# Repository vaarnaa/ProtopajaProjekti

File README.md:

# Prototype project

The project consists of a prototype for a local air cleaner device with IoT features. The prototype was built in the summer 2017 at the Aalto University's Protocamp course in co-operation with Consair Oy. The primary purpose of the device is to reduce construction workers exposure to waste particles while mixing mortar.

## How it works

### Mechanics

The enclosure of the device was built of plywood with the help of a 3D model. The air flow enters through the air vent in the front panel, passes through the filters in the middle and the fan in the rear of the device and then exits through the roof outlet.

### Microcontroller

The operation of the device is controlled by the microcontroller. It reads the values measured by the pressure sensors and adjusts the fan speed based on the measurement results. The airflow passing through the device is kept constant regardless of the degree of clogging of the filters.

### PID Control

The fan speed is controlled by a specific piece of software in the microcontroller. The code-based PID controller adjusts the speed to the desired value based on the difference between the measured and the desired speed.

### Networking

While the device is in operation, the GSM module connects to the server and transmits information about the status of the device. The server stores the data in the database. The person in charge of the device is informed by email or text message if the filters are clogged.

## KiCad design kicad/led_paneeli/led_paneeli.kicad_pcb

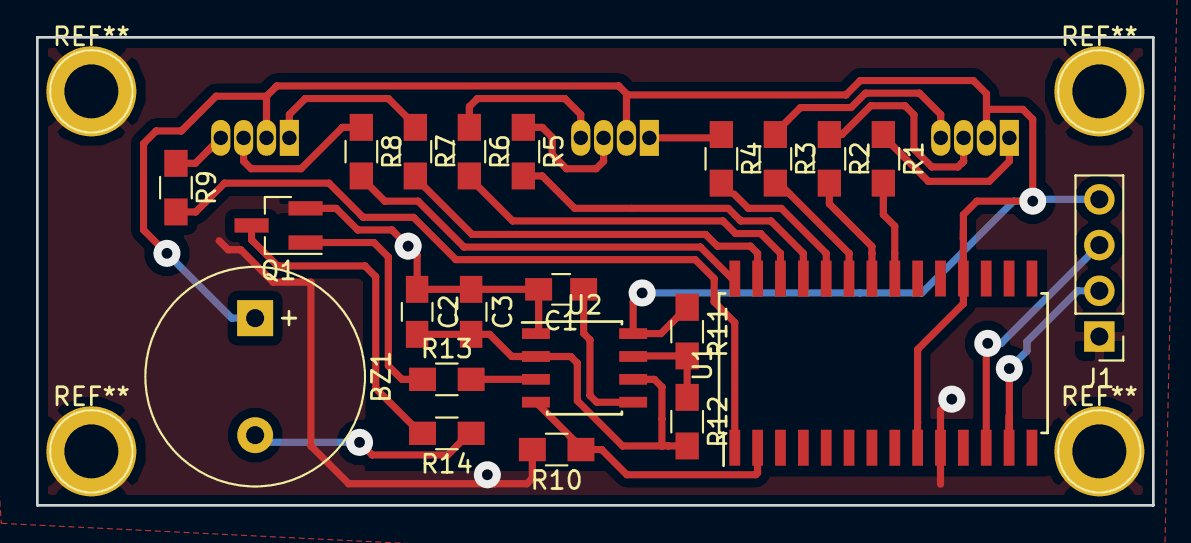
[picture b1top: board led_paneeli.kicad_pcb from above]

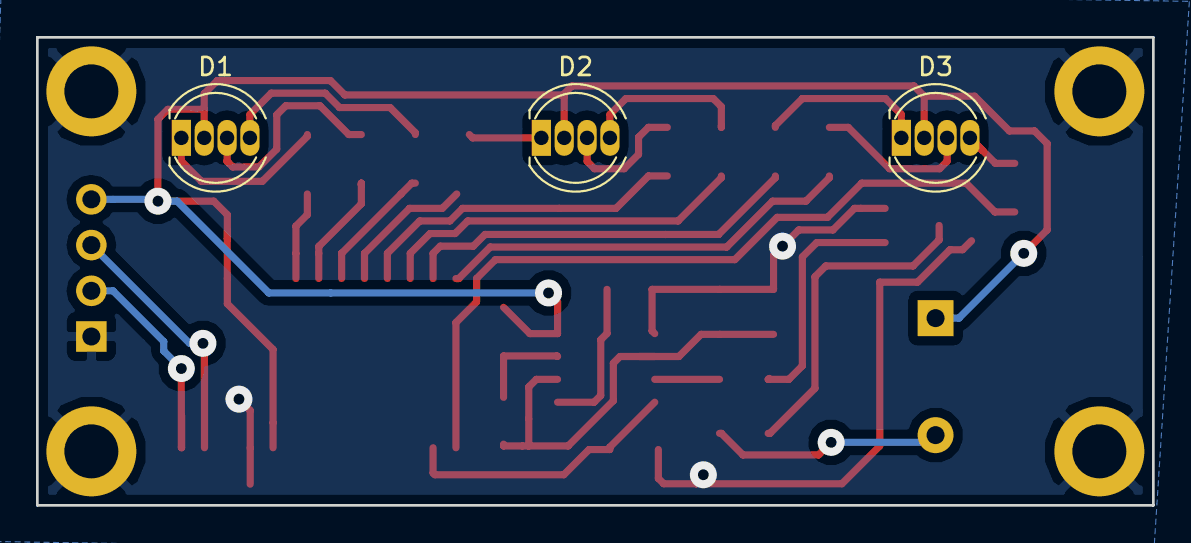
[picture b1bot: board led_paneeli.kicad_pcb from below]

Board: 2 copper layers, 62.0 x 26.0 mm, 25 parts (3 on the bottom side), 30 nets.

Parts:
BZ1: Buzzer; MagneticBuzzer_ProSignal_ABT-410-RC
C1: 10n; C_0805_HandSoldering
C2: 33n; C_0805_HandSoldering
C3: 22n; C_0805_HandSoldering
D1, D2, D3: LED_RAGB; LED_D5.0mm-4
J1: CONN_01X04; Pin_Header_Straight_1x04_Pitch2.54mm
Q1: PMV20XNE; SOT-23_Handsoldering
R1, R4, R7: 640; R_0805_HandSoldering
R2, R5, R8: 1k86; R_0805_HandSoldering
R3, R6, R9: 4k6; R_0805_HandSoldering
R10: 10k; R_0805_HandSoldering
R11: 1k; R_0805_HandSoldering
R12: 6k8; R_0805_HandSoldering
R13, R14: 330; R_0805_HandSoldering
U1: MCP23017; SOIC-28W_7.5x17.9mm_Pitch1.27mm
U2: NE555; SOIC-8_3.9x4.9mm_Pitch1.27mm

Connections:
+5V: BZ1.1, D1.2, D2.2, D3.2, J1.4, R11.1, U1.9, U1.18, U2.8
GND: C1.2, C2.1, C3.1, J1.1, Q1.2, R10.2, U1.10, U2.1
unnamed: BZ1.2, R14.1
unnamed: C1.1, U2.5
unnamed: C2.2, C3.2, R12.2, U2.2, U2.6
unnamed: D1.1, R1.1
unnamed: D1.3, R2.1
unnamed: D1.4, R3.1
unnamed: D2.1, R4.1
unnamed: D2.3, R5.1
unnamed: D2.4, R6.1
unnamed: D3.1, R7.1
unnamed: D3.3, R8.1
unnamed: D3.4, R9.1
unnamed: J1.2, U1.13
unnamed: J1.3, U1.12
unnamed: Q1.1, R13.1
unnamed: Q1.3, R14.2
unnamed: R1.2, U1.21
unnamed: R2.2, U1.22
unnamed: R3.2, U1.23
unnamed: R4.2, U1.24
unnamed: R5.2, U1.25
unnamed: R6.2, U1.26
unnamed: R7.2, U1.27
unnamed: R8.2, U1.28
unnamed: R9.2, U1.1
unnamed: R10.1, U1.2, U2.4
unnamed: R11.2, R12.1, U2.7
unnamed: R13.2, U2.3

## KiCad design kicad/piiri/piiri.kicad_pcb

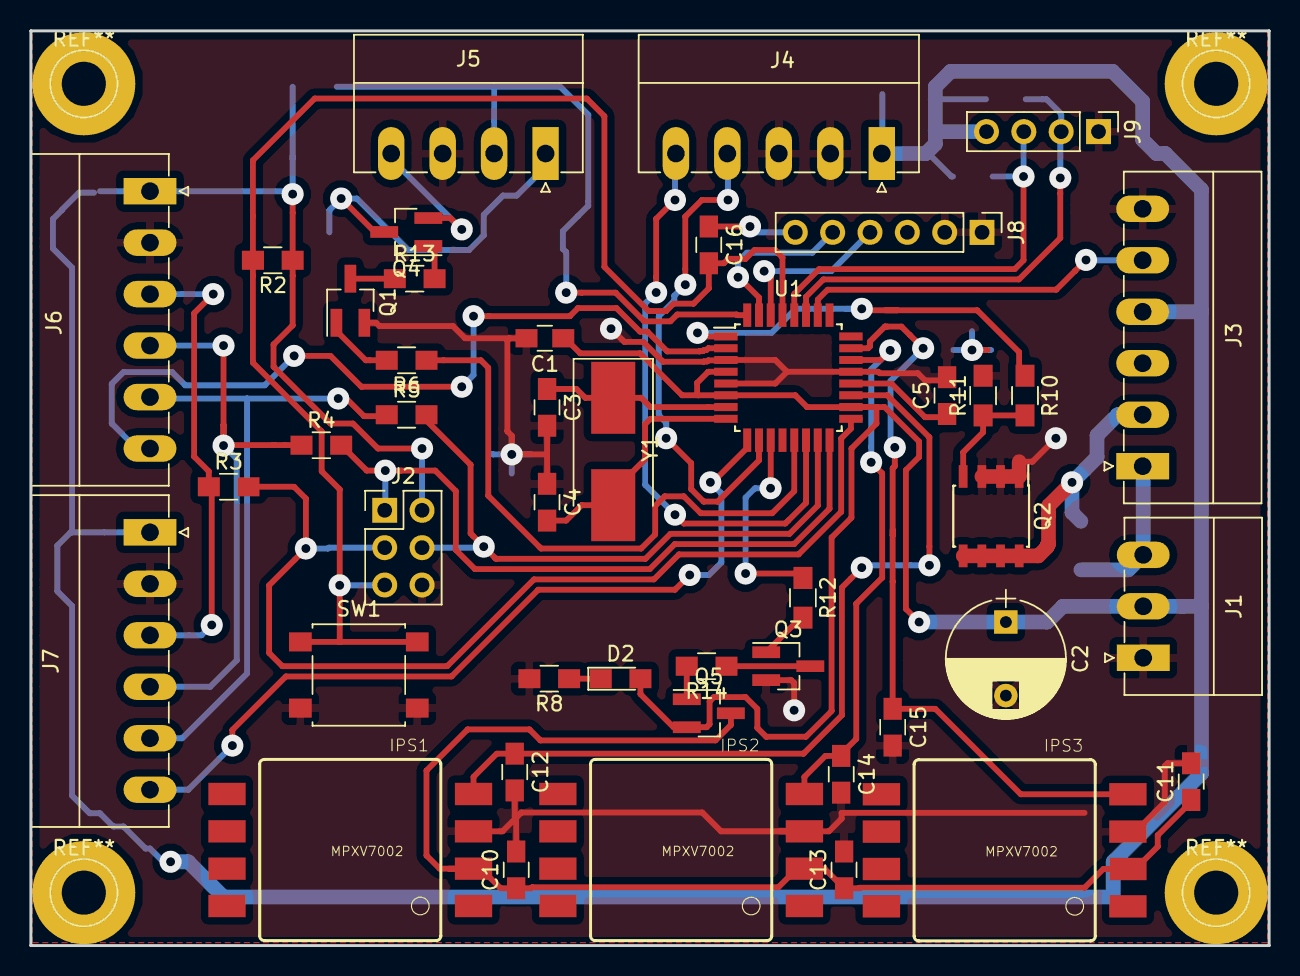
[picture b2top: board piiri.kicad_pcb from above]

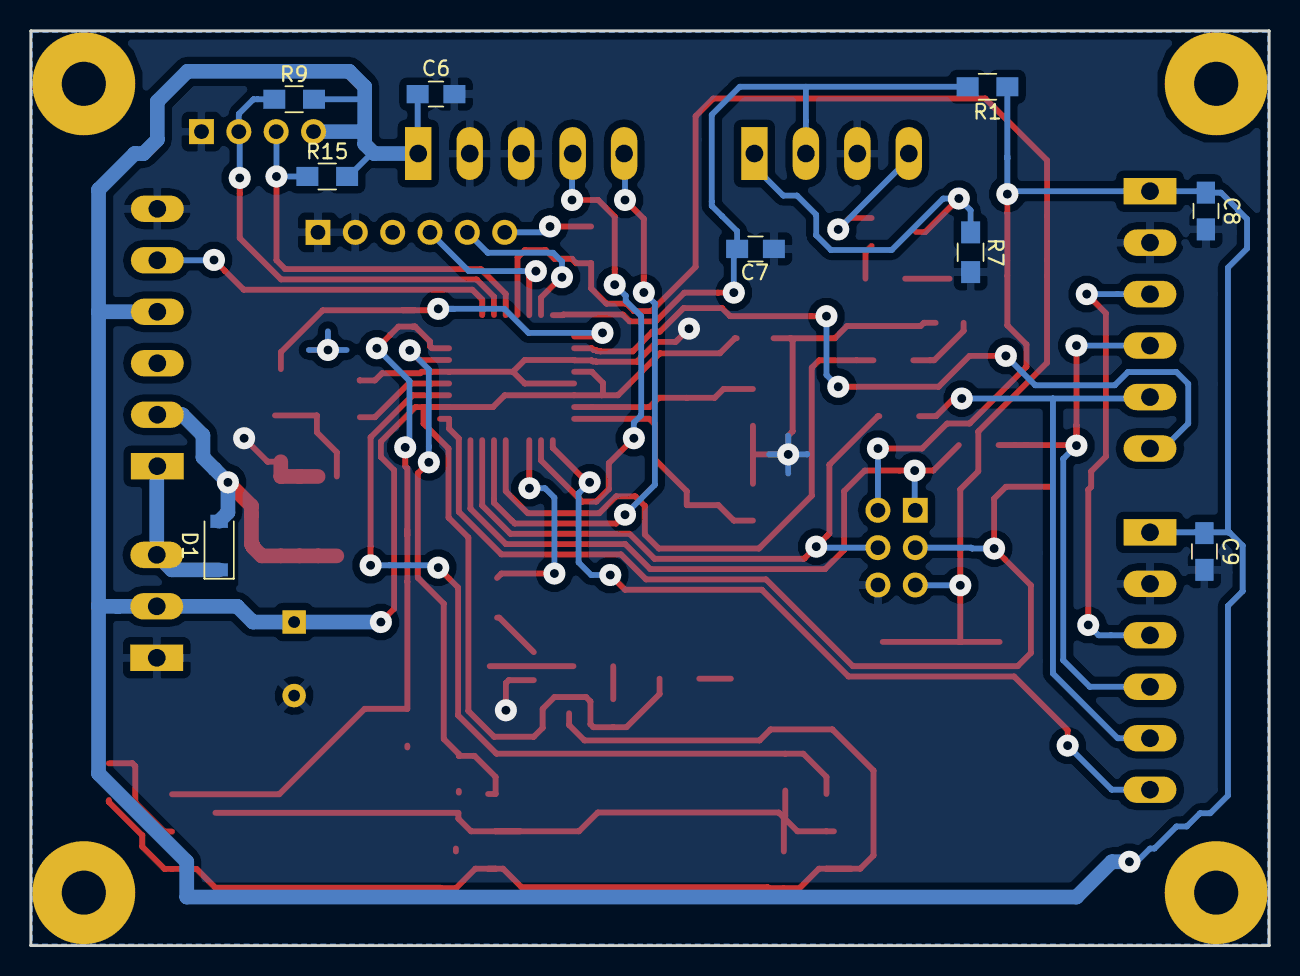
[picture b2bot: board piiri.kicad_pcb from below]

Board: 2 copper layers, 84.2 x 62.2 mm, 53 parts (9 on the bottom side), 42 nets.

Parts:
C1, C6, C7, C8, C9, C10, C11, C13, C16: 0.1uF; C_0805_HandSoldering
C2: 220uF; CP_Radial_D8.0mm_P5.00mm
C3, C4: 22pF; C_0805_HandSoldering
C5: 10nF; C_0805_HandSoldering
C12, C14, C15: 470pF; C_0805_HandSoldering
D1: D; D_SOD-123
D2: LED; LED_0805_HandSoldering
IPS1, IPS2, IPS3: MPXV7002; SOP8-1351
J1: VIRTA; PhoenixContact_MC-G_03x3.50mm_Angled
J2: ICSP; Pin_Header_Straight_2x03_Pitch2.54mm
J3: I/O; PhoenixContact_MC-G_06x3.50mm_Angled
J4: GSM; PhoenixContact_MC-G_05x3.50mm_Angled
J5: MOOTTORI; PhoenixContact_MC-G_04x3.50mm_Angled
J6: ANTURI1; PhoenixContact_MC-G_06x3.50mm_Angled
J7: ANTURI2; PhoenixContact_MC-G_06x3.50mm_Angled
J8: CONN_01X06; Pin_Header_Straight_1x06_Pitch2.54mm
J9: CONN_01X04; Pin_Header_Straight_1x04_Pitch2.54mm
Q1, Q3: BC818-40; SOT-23_Handsoldering
Q2: STS6NF20V; SOIC-8_3.9x4.9mm_Pitch1.27mm
Q4, Q5: BC578; SOT-23_Handsoldering
R1, R2, R6, R7, R11, R12, R13, R14: 10k; R_0805_HandSoldering
R3, R4, R5, R10: 560R; R_0805_HandSoldering
R8: 1k; R_0805_HandSoldering
R9, R15: 4k7; R_0805_HandSoldering
SW1: SW_Push; SW_SPST_B3S-1000
U1: ATMEGA328P-AU; TQFP-32_7x7mm_Pitch0.8mm
Y1: 16MHz; Crystal_SMD_7050-2pin_7.0x5.0mm_HandSoldering

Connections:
+5V: C1.1, C2.1, C6.1, C8.1, C9.1, D2.2, J1.2, J2.2, J3.4, J4.1, J6.1, J7.1, J9.4, Q5.2, R1.1, R2.1, R9.2, R15.2, U1.4, U1.6, U1.18
+12V: D1.1, J1.3, J3.1
GND: C1.2, C2.2, C3.2, C4.1, C5.2, C6.2, C7.2, C8.2, C9.2, C10.2, C11.2, C12.2, C13.2, C14.2, C15.2, IPS1.3, IPS2.3, IPS3.3, J1.1, J2.6, J3.6, J4.2, J4.3, J5.3, J6.2, J7.2, J8.1, J8.2, J9.1, Q1.2, Q2.1, Q2.2, Q2.3, Q3.2, R7.2, R8.2, R11.2, SW1.2, U1.3, U1.5, U1.21
IPS_A: C12.1, IPS1.4, U1.19
IPS_B: C14.1, IPS2.4, U1.22
IPS_C: C15.1, IPS3.4, U1.23
IPS_ON: R12.1, U1.11
IPS_PWR: C10.1, C11.1, C13.1, IPS1.2, IPS2.2, IPS3.2, Q5.3
MISO: J6.4, J7.4, R4.1
MOSI: J6.5, J7.5, R5.1
unnamed: C3.1, U1.7, Y1.1
unnamed: C4.2, U1.8, Y1.2
unnamed: C5.1, U1.20
unnamed: C16.1, J8.6
unnamed: D1.2, J3.2, Q2.5, Q2.6, Q2.7, Q2.8
unnamed: D2.1, R8.1
unnamed: J2.1, R4.2, U1.16
unnamed: J2.3, R3.2, U1.17
unnamed: J2.4, R5.2, U1.15
unnamed: J5.1, Q4.3, R7.1
unnamed: J5.4, Q4.2
unnamed: Q1.1, R6.2
unnamed: Q1.3, R13.1
unnamed: Q2.4, R10.2, R11.1
unnamed: Q3.1, R12.2
unnamed: Q3.3, R14.1
unnamed: Q4.1, R13.2
unnamed: Q5.1, R14.2
OCOUT: C7.1, J5.2, R1.2, U1.32
PWM: R6.1, U1.13
RESET: C16.2, J2.5, R2.2, SW1.1, U1.29
RXD: J8.4, U1.30
SCK: J6.3, J7.3, R3.1
SCL: J9.3, R15.1, U1.28
SDA: J9.2, R9.1, U1.27
SS1: J6.6, U1.2
SS2: J7.6, U1.9
SW: J3.5, U1.26
S_RX: J4.5, U1.14
S_TX: J4.4, U1.10
TXD: J8.5, U1.31
VLED: R10.1, U1.1

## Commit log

2017-07-12 Added UnicodError handling
2017-07-19 Added logging and timeout for connections not sending any data
2017-07-20 Update serveri.py
    Muutettu main-funktioksi
2017-07-25 Several improvements
2017-07-25 small fix
2017-07-27 Connection Error handling
2017-07-27 init_server()
2017-07-29 send_email() update
2017-07-29 data_to_db() updates relevant table now
2017-07-30 added find_preference()
2017-08-23 3D Model
    Creo 3D Model files
2017-08-23 Mikrokontrollerin koodi
    ATmega328P mikrokontrollerin ohjaamiseen. Tehty Arduino IDE:ssä.
2017-08-24 send_email() improvement
2017-08-24 PCB
    PCB
2017-08-24 Create LICENSE
2017-08-24 Pääohjelma
    Arduinokoodia
2017-08-24 GSM-moduulin ohjaamiseen
    Toimii yhdessä pääohjelman kanssa
2017-08-24 Pääohjelma
2017-09-17 Mikrokontrollerin pääohjelma
2018-11-07 Added website files
2018-11-07 Changed img links
2018-11-07 Changed README.me file
